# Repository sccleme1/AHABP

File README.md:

# AHABP
Autonomous High-Altitude Balloon Payload

This github repository is for EEE 488/489 Senior Design I and II for electrical engineering.

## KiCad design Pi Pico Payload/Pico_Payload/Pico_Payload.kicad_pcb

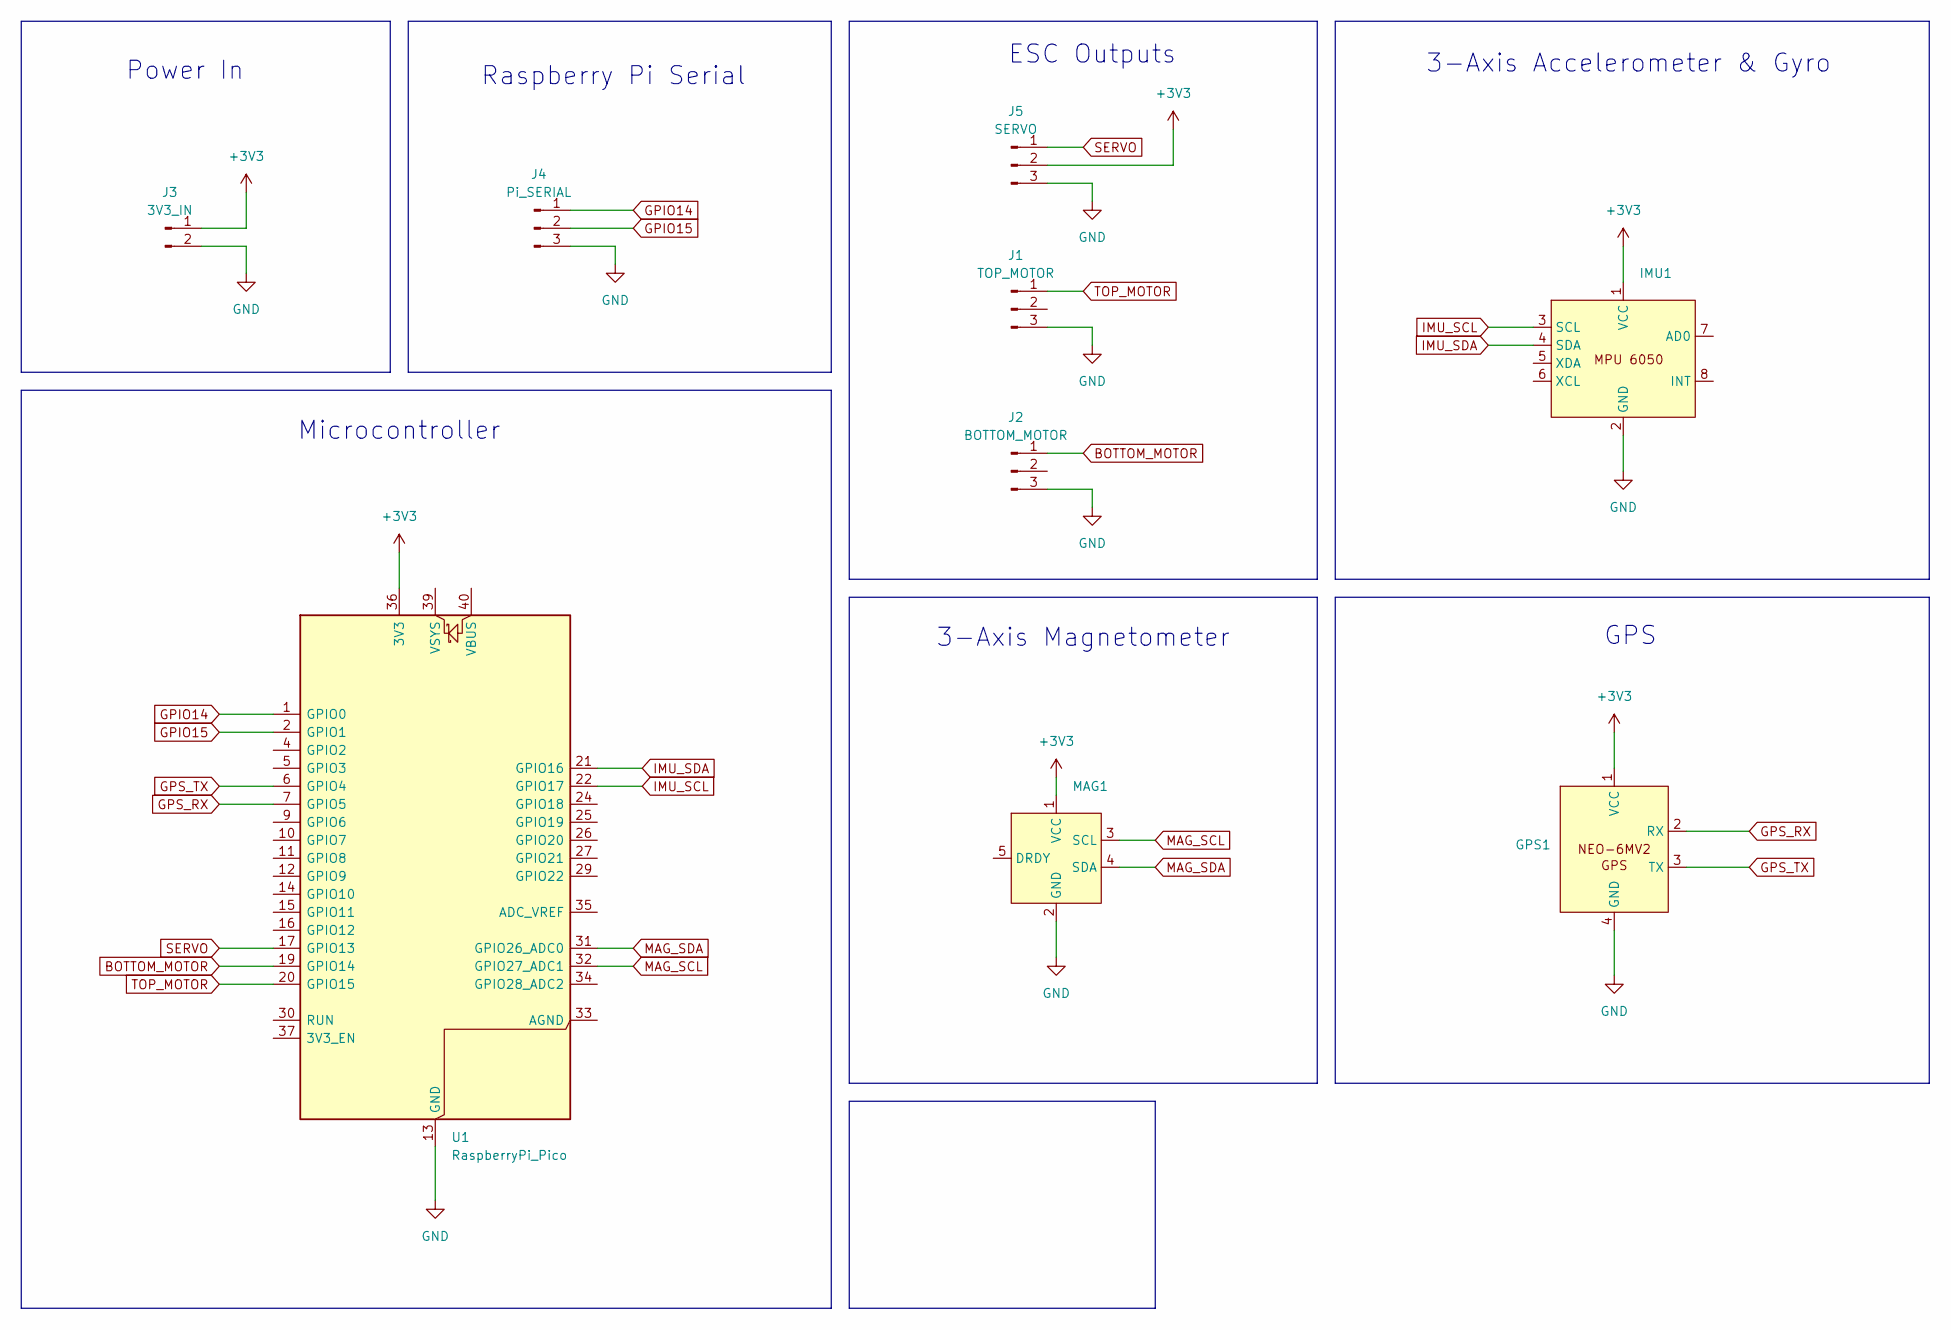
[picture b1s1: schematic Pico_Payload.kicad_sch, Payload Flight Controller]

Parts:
GPS1: PinHeader_1x04_P1.27mm_Vertical
IMU1: PinHeader_1x08_P1.27mm_Vertical
J1: TOP_MOTOR; PinHeader_1x03_P1.27mm_Vertical
J2: BOTTOM_MOTOR; PinHeader_1x03_P1.27mm_Vertical
J3: 3V3_IN; PinHeader_1x02_P1.27mm_Vertical
J4: Pi_SERIAL; PinHeader_1x03_P1.27mm_Vertical
J5: SERVO; PinHeader_1x03_P1.27mm_Vertical
MAG1: PinHeader_1x05_P1.27mm_Vertical
U1: RaspberryPi_Pico; RaspberryPi_Pico_Original_SMD_MountingHoles_Castellated_Han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

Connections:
+3V3: GPS1.1 (VCC), IMU1.1 (VCC), J3.1, J5.2, MAG1.1 (VCC), U1.36 (3V3)
BOTTOM_MOTOR: J2.1, U1.19 (GPIO14)
GND: GPS1.4 (GND), IMU1.2 (GND), J1.3, J2.3, J3.2, J4.3, J5.3, MAG1.2 (GND), U1.3 (GND), U1.8 (GND), U1.13 (GND), U1.18 (GND), U1.23 (GND), U1.28 (GND), U1.38 (GND)
GPIO14: J4.1, U1.1 (GPIO0)
GPIO15: J4.2, U1.2 (GPIO1)
GPS_RX: GPS1.2 (RX), U1.7 (GPIO5)
GPS_TX: GPS1.3 (TX), U1.6 (GPIO4)
IMU_SCL: IMU1.3 (SCL), U1.22 (GPIO17)
IMU_SDA: IMU1.4 (SDA), U1.21 (GPIO16)
MAG_SCL: MAG1.3 (SCL), U1.32 (GPIO27_ADC1)
MAG_SDA: MAG1.4 (SDA), U1.31 (GPIO26_ADC0)
SERVO: J5.1, U1.17 (GPIO13)
TOP_MOTOR: J1.1, U1.20 (GPIO15)

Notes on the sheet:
3-Axis Accelerometer & Gyro
3-Axis Magnetometer
ESC Outputs
Raspberry Pi Serial
Power In
Microcontroller
GPS

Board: 2 copper layers, 9 parts (0 on the bottom side), 13 nets, no tracks yet.

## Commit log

2023-11-08 Update main.py
    Changed to incorporate interrupts on rising and falling edge
2023-11-08 Update main.py
    updated
2023-11-09 Update main.py
    couldn't get to work; still shows 0 revolutions
2023-11-09 Update main.py
    works
2023-11-14 added SD card reader
2024-02-27 updated
    added live tracking script
2024-02-29 added pysolar
2024-03-13 added ephem tests
2024-03-14 IMU drop test
2024-03-15 new drop test
2024-03-21 opencv tests
2024-03-21 updated ephem
2024-04-08 pico payload update
2024-04-24 reorganized
